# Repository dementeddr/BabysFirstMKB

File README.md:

# Baby's First Mechanical Keybaord
An RGB mechanical keyboard that consists of a single oversized key. It's a perfect first keyboard for a small child! Plug it in to a computer and it will function as an ENTER key. Bonus Fun Mode: Plug it into a computer while holding the key down. Keep the key pressed until all four LEDs light up. Then put your cursor in a text box and see what happens.

### REPO CONTENTS
- Arduino code 
- KiCAD PCB files
- Fusion 360 project files for the 3D printed case

### OTHER MATERIALS
- 1x Novelkeys Big Switch (https://novelkeys.com/products/the-big-switch-series)
- 1x Seeeduino Xiao microcontroller
- 4x 5V LEDs (Red, Green, Blue, & Yellow recommended)
- PLA Filament
- 4x 220 Ohm resistors
- 4x M3x6mm screws
- 8x M3 screws (anything between 6 and 12 mm)
- 2x 16-14 AWG female spade electrial connectors
- 1x 7-pin header
- 1x 6-pin header
- Wire and solder

### ASSEMBLY NOTES: 
To mount the microcontroler: The Seeeduino Xiao is placed flat on the PCB, covering the PCB's serial number, with the USB C port sticking off the wide end of the board. The long side of the bin headers are stuck through both Xiao and PCB* and soldered in place, then the plastic headers are snipped off. This is to keep the Xiao board firmly in place, even if the port suffers some... child-like abuse.

The two electrical connectors are used as swappable dry contacts for the Big Switch. Use a knife or wire cutters to cut off the plastic insulation, then some needlenose pliars to squeeze the round end smaller. Strip the end of a wire and stick it into the round part from the spade end, then solder it into place. Then you just shove the round end into the appropriate holes on the printed base. You'll need to fold the spade end of one of the connectors slightly, so it can maintain contact with the thin pin on the Big Switch (the thin, bendy, copper-colored one). 

* When I designed the PCB to mount the Seeeduino Xiao on, by mistake I connected the copper channel for the red LED to the 3v3 Power pin on the Xiao instead of a data pin. So I changed the code to make the red LED pin #7 and soldered the connecting wire to the pin directly. When putting the pin headers through the pinholes, use the 7-pin header through the 0-6 pins, and the 6-pin header through the 8-VCC pins. LEAVE THE #7 PIN EMPTY, and instead fill it with a wire directly to the Red LED connector.

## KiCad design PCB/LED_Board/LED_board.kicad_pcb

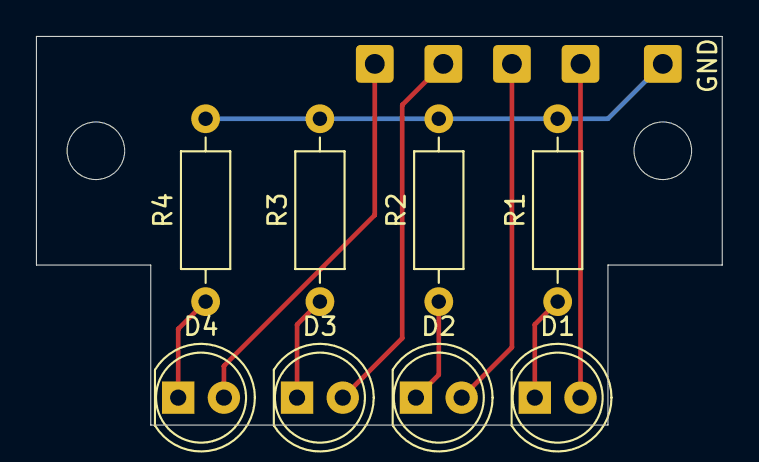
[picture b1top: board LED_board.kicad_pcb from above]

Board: 2 copper layers, 38.1 x 21.6 mm, 9 parts (0 on the bottom side), 5 nets.

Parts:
D1, D2, D3, D4: LED; LED_D5.0mm
GND: SolderWire-0.5sqmm_1x01_D0.9mm_OD2.1mm
R1, R2, R3, R4: 220; R_Axial_DIN0207_L6.3mm_D2.5mm_P10.16mm_Horizontal

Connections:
GND: GND.1, R1.2, R2.2, R3.2, R4.2
unnamed: D1.1, R1.1
unnamed: D2.1, R2.1
unnamed: D3.1, R3.1
unnamed: D4.1, R4.1

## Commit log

2022-09-19 First commit, with nearly completed project
2022-10-17 Update README.md
    Added materials list and pictures
2022-10-17 Added usage explanation to Readme
